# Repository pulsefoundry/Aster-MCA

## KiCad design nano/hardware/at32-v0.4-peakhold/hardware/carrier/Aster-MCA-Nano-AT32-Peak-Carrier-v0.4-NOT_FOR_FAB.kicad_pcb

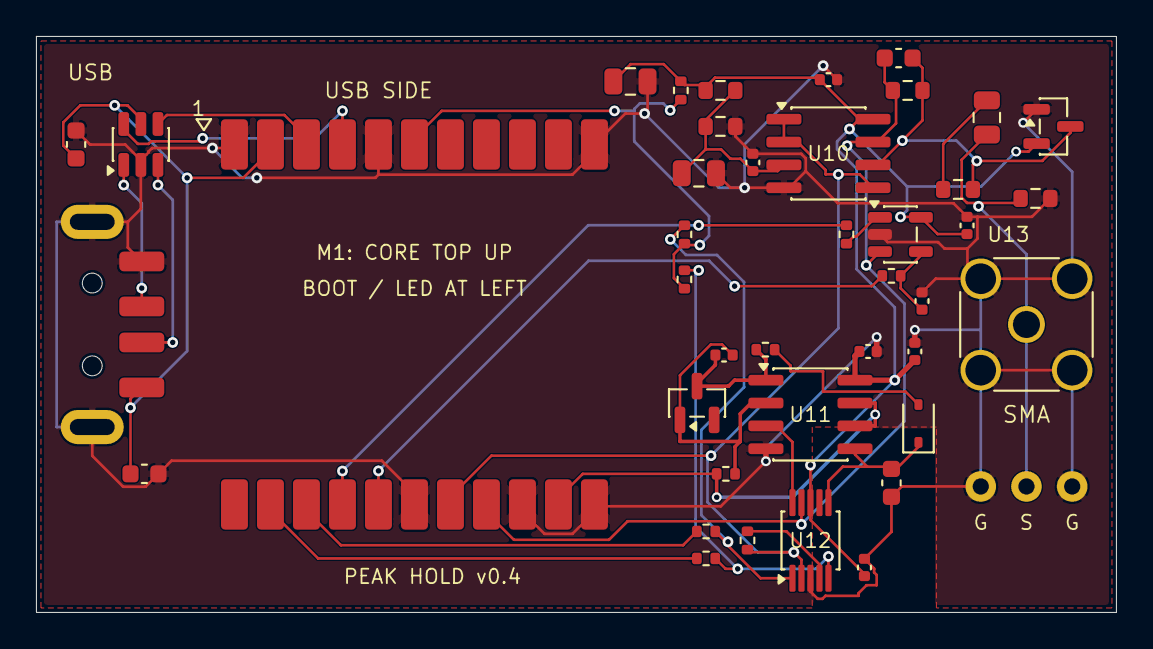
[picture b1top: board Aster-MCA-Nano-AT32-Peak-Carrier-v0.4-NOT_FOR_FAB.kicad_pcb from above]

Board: 2 copper layers, 60.0 x 32.0 mm, 42 parts (0 on the bottom side), 29 nets.

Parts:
C90: 1u X7R 10V; C_0603_1608Metric
C91: 100n X7R 10V; C_0603_1608Metric
C100: 33n C0G 50V; C_0805_2012Metric
C101: DNP 1p-4.7p C0G; C_0603_1608Metric
C102: 470p C0G 50V; C_0603_1608Metric
C103: DNP 0.5p-4.7p C0G; C_0402_1005Metric
C104: 10n X7R; C_0402_1005Metric
C105, C107: 10u X7R 10V; C_0805_2012Metric
C106, C108, C109, C111, C112: 100n X7R; C_0402_1005Metric
C110: 1u X7R; C_0402_1005Metric
D10: BAV199,215; SOT-23
D11: BAS316,115; D_SOD-323
D12: BAS70-04,215; SOT-23
D90: USBLC6-2SC6; SOT-23-6
J1: USB-A_MALE_CNCTech_1001-011-01101_PATTERN; USB_A_CNCTech_1001-011-01101_Horizontal
J2: SMA_F_5PIN_5.08MM_PATTERN; SMA_Amphenol_132134_Vertical
J3: G-S-G_WIRE_PADS_2.54; Aster_GSG_Wire_3P
M1: AT32_CORE_v0.4_26x20; Aster_AT32_Core_22_26x20_Carrier
R100: 0R; R_0402_1005Metric
R101: 43k 0.1%; R_0603_1608Metric
R102: 10k 0.1%; R_0603_1608Metric
R103: 1M; R_0603_1608Metric
R104, R105: 49.9k 0.1%; R_0603_1608Metric
R106: 22R; R_0402_1005Metric
R107: 1k; R_0402_1005Metric
R108: 330R; R_0402_1005Metric
R109, R110: 100k; R_0402_1005Metric
R111, R112: 100R; R_0402_1005Metric
R113: 10k; R_0402_1005Metric
R114: 33R; R_0402_1005Metric
U10: TLV9062IDR; SOIC-8_3.9x4.9mm_P1.27mm
U11: OPA2356AIDR; SOIC-8_3.9x4.9mm_P1.27mm
U12: TMUX1136DGSR; MSOP-10_3x3mm_P0.5mm
U13: TLV3201AIDBVR; SOT-23-5

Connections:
AV3V3: C107.1, C108.1, C109.1, C110.1, C111.1, C112.1, D10.2, R100.2, R101.1, U10.8, U11.8, U12.8, U13.5
BASE_ADC: M1.16, R108.1, U10.1, U10.2, U10.5, U12.2
BASE_DIV: C105.1, C106.1, R101.2, R102.1, U10.3
CAPTURE_IN: U11.3, U12.10
DAC_THRESH: M1.18, R113.1
GND: C90.2, C91.2, C102.2, C104.2, C105.2, C106.2, C107.2, C108.2, C109.2, C110.2, C111.2, C112.2, D10.1, D90.2, J1.4, J1.SH, J2.2, J3.1, J3.3, M1.1, M1.5, M1.11, M1.12, M1.14, M1.17, R102.2, R103.2, U10.4, U11.4, U12.3, U13.2
HOLD: M1.20, R111.1
HOLD_CAP: C102.1, D11.1, U11.5, U12.6
HOLD_CTL: R109.2, R111.2, U12.1
INPUT_AC: C100.2, R104.1
INPUT_FB: C101.2, D10.3, R104.2, R105.2, U10.6
PEAK_ADC: M1.13, R107.1, U11.6, U11.7
PEAK_DIODE_A: D11.2, R106.2
PEAK_DRV: C103.1, D12.3, R106.1, U11.1
PEAK_FB: C103.2, D12.1, R107.2, U11.2
PEAK_RESET: M1.21, R112.1
PULSE_IN: C100.1, J2.1, J3.2, R103.1
RAW_ADC: C101.1, M1.15, R105.1, U10.7, U12.9, U13.3
RESET_CTL: R110.2, R112.2, U12.5
RESET_SOURCE: R108.2, U12.4
THRESH_FILT: C104.1, R113.2, U13.4
TRIG: M1.19, R114.2
TRIG_DRV: R114.1, U13.1
USB_DM: D90.4, M1.3
USB_DM_CONN: D90.3, J1.2
USB_DP: D90.6, M1.4
USB_DP_CONN: D90.1, J1.3
V3V3: M1.6, R100.1, R109.1, R110.1
VBUS: C90.1, C91.1, D90.5, J1.1, M1.2

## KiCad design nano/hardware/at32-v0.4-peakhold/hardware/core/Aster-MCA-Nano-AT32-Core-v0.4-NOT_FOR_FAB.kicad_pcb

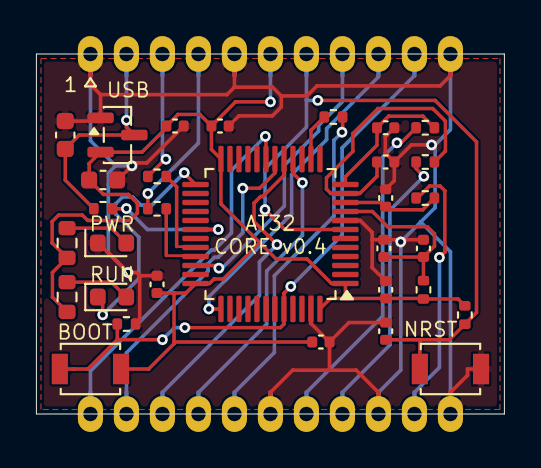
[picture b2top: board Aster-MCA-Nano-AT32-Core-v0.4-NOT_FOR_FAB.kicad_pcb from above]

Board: 2 copper layers, 26.0 x 20.0 mm, 32 parts (0 on the bottom side), 28 nets.

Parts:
C1: 1u X7R 10V; C_0603_1608Metric
C2: 4.7u X7R 10V; C_0603_1608Metric
C3, C4, C5, C6, C8, C10: 100n X7R 10V; C_0402_1005Metric
C7, C9: 1u X7R 10V; C_0402_1005Metric
C11, C13: 1n C0G 50V; C_0402_1005Metric
C12: 100p C0G 50V; C_0402_1005Metric
J1: CASTELLATED_22_26x20; Aster_Castellated_22_26x20
LED1, LED2: BLUE_0603_USER_STOCK; LED_0603_1608Metric
R1, R2: 1k 1%; R_0603_1608Metric
R3, R4, R5: 10k 1%; R_0402_1005Metric
R6, R11, R12: 0R; R_0402_1005Metric
R7, R9: 100R 1%; R_0402_1005Metric
R8, R10: 33R 1%; R_0402_1005Metric
SW1, SW2: B3U-1000P; SW_SPST_B3U-1000P
U1: AT32F423CCT7; LQFP-48_7x7mm_P0.5mm
U2: XC6206P332MR-G; SOT-23

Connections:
ADC_BASE_PIN: C13.1, R9.2, U1.12
ADC_PEAK_PIN: C11.1, R7.2, U1.10
ADC_RAW_PIN: C12.1, R8.2, U1.11
AUX: J1.22, U1.19
BASE_ADC: J1.16, R9.1
BOOT0: J1.10, R3.1, SW1.1, U1.44
DAC_THRESH: J1.18, R10.2
DAC_THRESH_PIN: R10.1, U1.14
GND: C1.2, C2.2, C3.2, C4.2, C5.2, C6.2, C7.2, C8.2, C9.2, C10.2, C11.2, C12.2, C13.2, J1.1, J1.5, J1.11, J1.12, J1.14, J1.17, LED1.1, R3.2, SW2.2, U1.8, U1.47, U2.1
HOLD: J1.20, U1.17
LED_PWR_A: LED1.2, R1.2
LED_RUN: LED2.1, U1.25
LED_RUN_A: LED2.2, R2.2
MCU_USB_DM: R11.2, U1.32
MCU_USB_DP: R12.2, U1.33
NRST: C10.1, J1.7, R4.1, SW2.1, U1.7
PEAK_ADC: J1.13, R7.1
PEAK_RESET: J1.21, U1.18
RAW_ADC: J1.15, R8.1
SWCLK: J1.9, U1.37
SWDIO: J1.8, U1.34
TRIG: J1.19, U1.16
USB_DM: J1.3, R11.1
USB_DP: J1.4, R12.1
V3V3: C2.1, C3.1, C4.1, C5.1, C6.1, C7.1, J1.6, R1.1, R2.1, R4.2, R6.1, SW1.2, U1.1, U1.24, U1.36, U1.48, U2.2
VBUS: C1.1, J1.2, R5.1, U2.3
VBUS_SENSE: R5.2, U1.30
VDDA: C8.1, C9.1, R6.2, U1.9
